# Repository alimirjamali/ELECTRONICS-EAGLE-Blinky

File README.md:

# 555 Blinky SMD PCB
This was my 1st PCB in Eagle. I started learning Eagle following Jeremy Blum's Eagle Tutorial <a href="https://www.youtube.com/watch?v=1AXwjZoyNno&list=PL868B73617C6F6FAD"> Youtube</a>.

# License
This hardware is licensed under [Creative Commons Share Alike](http://creativecommons.org/licenses/by-sa/4.0/).

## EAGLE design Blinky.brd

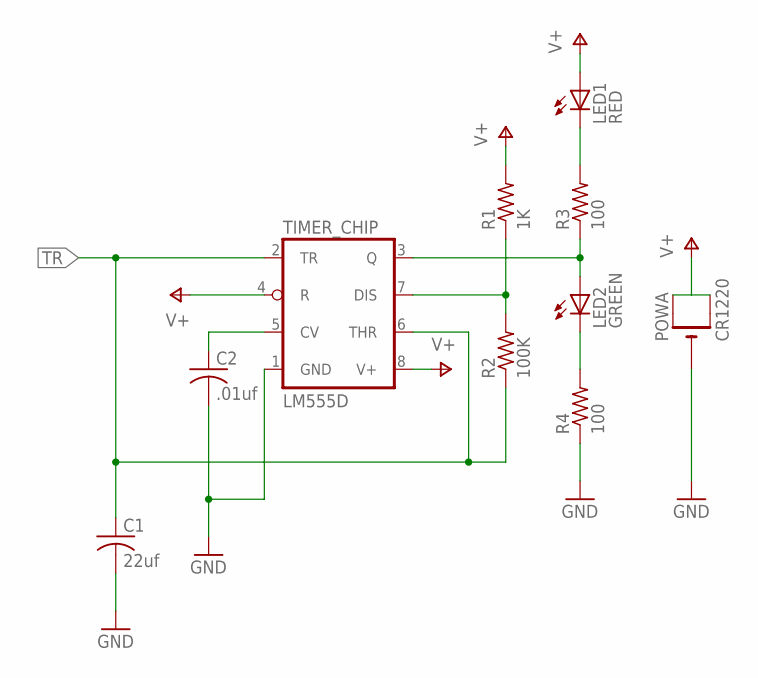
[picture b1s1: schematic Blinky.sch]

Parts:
C1: 22uf; C0805; MPN 08056D226MAT2A
C2: .01uf; C0805; MPN 08051A101J4T4A
LED1: RED; CHIP-LED0805; MPN MCL-S270SRC
LED2: GREEN; CHIP-LED0805; MPN OVS-0804
POWA: CR1220; CR1220-SMD; MPN S8411-45R
R1: 1K; R0805; MPN CRCW08051K00FKTA
R2: 100K; R0805; MPN CRCW0805100KFKTA
R3, R4: 100; R0805; MPN CRCW0805100RFKTA
TIMER_CHIP: LM555D; SO08; MPN SA555D

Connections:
GND: C1.2, C2.2, POWA.-, R4.1, TIMER_CHIP.1 (GND)
unnamed: LED1.C, R3.2
unnamed: LED2.A, R3.1, TIMER_CHIP.3 (Q)
unnamed: LED2.C, R4.2
unnamed: R1.1, R2.2, TIMER_CHIP.7 (DIS)
unnamed: C2.1, TIMER_CHIP.5 (CV)
TR: C1.1, R2.1, TIMER_CHIP.2 (TR), TIMER_CHIP.6 (THR)
V+: LED1.A, POWA.+$1 (+), POWA.+$2 (+1), R1.2, TIMER_CHIP.4 (R), TIMER_CHIP.8 (V+)

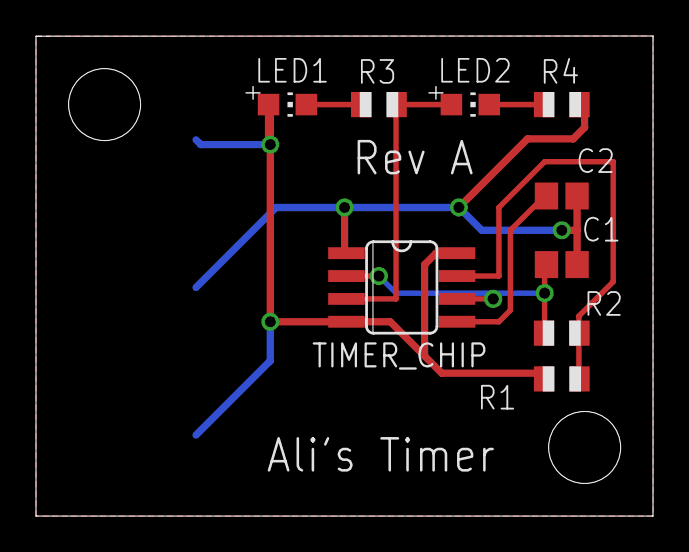
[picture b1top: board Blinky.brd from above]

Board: 2 copper layers, 34.3 x 26.7 mm, 10 parts (1 on the bottom side), 8 nets.
